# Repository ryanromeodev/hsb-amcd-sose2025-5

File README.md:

# Design and Implementation of Universal Biquad Filter

This project centers on the analog circuit design of a universal biquad filter targeting a corner frequency of 1 kHz and a quality factor (Q) of 10. The design process spans the complete development cycle—from initial specification and simulation to physical layout and hardware realization. Key phases include schematic design, functional modeling, simulation, and full PCB development.

Modern simulation environments and open-source platforms played a pivotal role throughout the project. The schematic capture and performance analysis—covering both frequency and time domains—were conducted using KiCad, which was also used for PCB layout and implementation. Functional modeling was performed using the Analog System Lab Kit (ASLK) and Red Pitaya, with the latter offering a flexible and cost-efficient solution for capturing frequency responses from ASLK-based implementations.

The project workflow is tightly integrated with reproducible tools such as Quarto, Jupyter Notebooks, Python, NumPy,Scipy, Control and Matplotlib for analysis, visualization, and documentation. Version control and collaboration were managed through Git, ensuring transparency and traceability at each stage.

Note: All design files, source code, and documentation are publicly available in our [GitHub repository](https://github.com/oreymaonr/hsb-amcd-sose2025-5).

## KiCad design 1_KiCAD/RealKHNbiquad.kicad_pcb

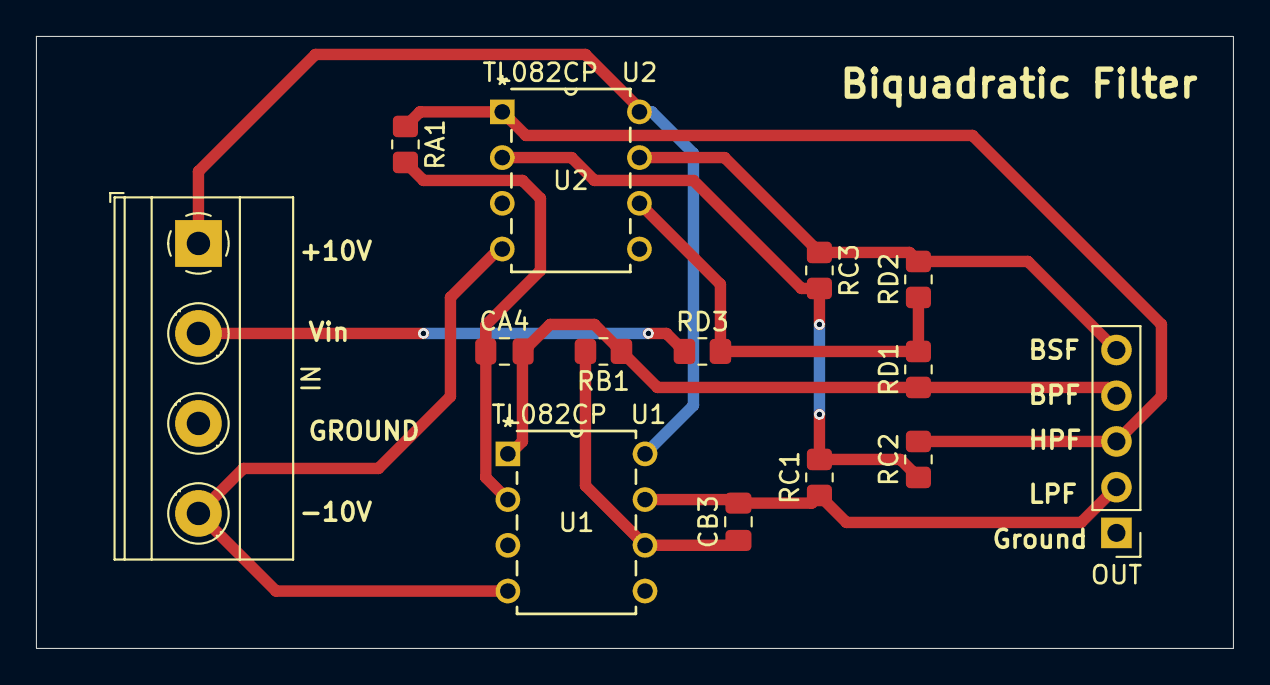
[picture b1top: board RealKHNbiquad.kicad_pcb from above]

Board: 2 copper layers, 66.5 x 34.0 mm, 14 parts (0 on the bottom side), 12 nets.

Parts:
CA4: 157n; C_0805_2012Metric_Pad1.18x1.45mm_HandSolder
CB3: 157n; C_0805_2012Metric_Pad1.18x1.45mm_HandSolder
IN: Screw_Terminal_01x04; TerminalBlock_Phoenix_MKDS-1,5-4_1x04_P5.00mm_Horizontal
OUT: Conn_01x05_Pin; PinHeader_1x05_P2.54mm_Vertical
RA1: 1k; R_0805_2012Metric_Pad1.20x1.40mm_HandSolder
RB1: 1k; R_0805_2012Metric_Pad1.20x1.40mm_HandSolder
RC1, RC2, RC3: 1k; R_0805_2012Metric_Pad1.20x1.40mm_HandSolder
RD1: 10k; R_0805_2012Metric_Pad1.20x1.40mm_HandSolder
RD2, RD3: 1k; R_0805_2012Metric_Pad1.20x1.40mm_HandSolder
U1, U2: TL082; P8

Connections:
/BPF: CA4.2, OUT.4, RB1.1, RD1.1, U1.1
/BSF: OUT.5, RC3.1, RD2.2, U2.7
/HPF: OUT.3, RA1.1, RC2.2, U2.1
/LPF: CB3.2, OUT.2, RC1.1, U1.7
GND: IN.3, OUT.1, U1.3 (+), U1.5 (+), U2.3 (+), U2.5 (+)
unnamed: CA4.1, RA1.2, U1.2 (-)
unnamed: CB3.1, RB1.2, U1.6 (-)
unnamed: RC1.2, RC2.1, RC3.2, U2.2 (-)
unnamed: RD1.2, RD2.1, RD3.2, U2.6 (-)
Vcc: IN.1, U1.8 (V+), U2.8 (V+)
Vee: IN.4, U1.4 (V-), U2.4 (V-)
Vin: IN.2, RD3.1

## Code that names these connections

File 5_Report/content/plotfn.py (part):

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        # fig, ax1 = plt.subplots(figsize=(10, 6))
        
        # # Plot Gain
        # line1, = ax1.plot(df['Time'], df['Voltage(BPF)'], 'b-', label='Voltage(BPF) /V')   
        # line2, = ax1.plot(df['Time'], df['Voltage(BSF)'], 'g-', label='Voltage(BSF) /V')   
        # line3, = ax1.plot(df['Time'], df['Voltage(HPF)'], 'r-', label='Voltage(HPF) /V')   
        # line4, = ax1.plot(df['Time'], df['Voltage(LPF)'], 'y-', label='Voltage(LPF) /V')   
        # ax1.set_xlabel('Time /s')
        # ax1.set_ylabel('Voltage /V')
        # # Combine legends from both axes
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
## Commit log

2025-04-30 init quarto
2025-04-30 added biQuad
2025-04-30 added TL082 spec
2025-05-02 quarto init
2025-05-02 kicad schematic
2025-05-02 image addition and image directory
2025-05-02 readme file
2025-05-02 adding graphs
2025-05-04 Design of KHN
2025-05-04 reverting changes
2025-05-07 new approach & khn test
2025-05-10 KHN Biquad
2025-05-10 KHN plots
2025-05-10 ignore
2025-05-10 H_0 resistor value
2025-05-13 tow thomas renewed
2025-05-13 tow thomas image addition
2025-05-13 image updated
2025-06-18 Added report
2025-06-18 file refactoring
2025-06-22 basics and tf's
2025-06-25 filter design and charecterestics basics
2025-06-28 updated graph generation template
2025-06-29 skeletoin done
2025-06-30 graphs initial optimization
2025-06-30 red pitaya plots
2025-07-13 updated to latest functions
2025-07-13 data for Transcients
2025-07-13 updated cleanup
2025-07-14 basics of filter design
2025-07-14 image added
2025-07-15 added kicad transcient analysis data
2025-07-15 added pcb circuit plots
2025-07-15 loepass-highpass
2025-07-15 Types of filters and rspective images
2025-07-15 Filters Types and images
2025-07-15 transcients csv from kicad
2025-07-15 keytranscients
2025-07-16 filter design updates
2025-07-16 introduction update
2025-07-16 image in main update
2025-07-16 charecterisation
2025-07-16 introimages
2025-07-16 refactoring
2025-07-16 PCB Images
2025-07-16 cleanup
2025-07-16 image mirroing
2025-07-16 KiCad Circuit
2025-07-16 index
2025-07-16 references
2025-07-16 introduction
2025-07-16 IntroductionFinal
2025-07-16 text changes
2025-07-16 typo
2025-07-16 refactor
2025-07-16 typo and fns
2025-08-20 headingtypo
2025-08-20 adding _manuscipt
2025-08-20 undo adding manuscript
2025-08-20 uploading pdf of the repo
2025-09-01 readme data
2025-09-01 figure alignment
2025-09-01 image layout
2025-09-01 removing width
2025-09-01 captioning
2025-09-01 caption completion
2025-09-01 tabular images
2025-09-01 2D rendered View and 3 D of PCB
2025-09-01 removing html file
2025-09-01 Adding Abstract
2025-09-01 Clean up
2025-09-01 Complete Report as pdf
2025-09-01 Deleted
2025-09-01 Complete Report PDF
2025-09-02 Reorder file structure
2025-09-02 Del PDF report
2025-09-02 Report ready for publishing
2025-09-06 filter design image rendering issue
2025-09-06 Initializing gh-pages branch
2025-09-06 publishing init
2025-09-06 publish to correct location
2025-09-06 adding the source path
2025-09-06 renaming path
2025-09-06 adding files to docs
2025-09-23 gh-pages repo
2025-09-23 adding nojekyl
2025-09-23 readme edits
2025-09-23 adiitional nojekyll
2025-09-23 with running quarto publish
2025-09-23 unnecessary nojekyl
2025-09-23 init 2
2025-09-23 readme changes
